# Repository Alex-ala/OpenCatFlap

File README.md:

OpenCatFlap
=====

Work in progress...

Being fed up with SurePets cat flap requiring cloud connection to properly work, I decided to design my own flap.
The 3D model is intended to fit into the SurePet adapter already installed.

I want my flap to have at least these features:
1. Easily managable via an API and/or WebUI/MQTT
2. Powered by battery OR power plug!
3. Easy install via AP/Wifi
4. Motion detection on both sides of the flap to check on where a cat is and where it moves to
5. Light barrier that detects into which direction the flap got opened
6. Light barrier in both sides of the "tunnel" to check into which direction the cat moved
7. Independent control of mechanic in and out control. (My cats outsmart SureFlap by letting each other out/in)
8. Two RFID sensors to detect cats on each side and possibly both!
9. Modular design to easily remove the cover, the electronics and the mechanical parts without having to unscrew screws from the outside.

In addition to that the software should be capable of everything SureFlap is capable of, plus:
1. Set pets as "outdoor only"
2. Quickly and more easily set specific per-cat permissions
3. Manually "unlock once" option for each direction

Current state:
------
**Hardware:**

It is bases on an ESP32 (Arduino Nano ESP32 for development) with various sensors and two servos to lock/unlock.
The 3D model is ready to be tested and a printed version is already in use to debug the code. Slight adjustments to the
antenna design will be done in future.

Used vital parts:
- 2x PIR (motion detection): Panasonic AMN33111, testing with cheaper options
- 2x light barrier for flap detection: TCST 1103
- 2x light barrier for tunnel passage: IR LED + NE555 and TSOP18*38 and TSOP18*56
- 2x RFID reader: EM4095
- 2x Servo: DSM44

**Software:**

The software runs a main process that handles global configs and aggregates events reported by the two state machines.
After the last hardware overhaul, quite some work is to be done to update sensors and reading RFID from EM4095 instead of WL-134

## State machines
The locking and unlocking logic is split up into two independent state machines, one for each direction of travel.
One state machine handles the PIR, RFID and Servo on one side of the cat flap.

This way the flap can idependently unlock for ougoing or incoing cats without acidentally opening the other direction aswell, allowing false passages.

Roughly speaking there are 3 states: Idle (only PIR active to wait for motion), Reading (RFID enabled when motion is detected) and unlocked (when a correct RFID is read).

## Wifi

If no Wifi is configured, the flap acts as an AP opening an open "OpenCatFlap" wifi. One can either use this wifi for full control via api, or send credentials to connect to an existing wifi.

## MQTT

MQTT can be configured to connect to an existing MQTT server. The flap will then send events to topics `opencatflap/<flapname>/<type>`.
Configuration via MQTT is planned.

## Webserver

Current means to configure the flap is via http. There is a webserver running on :80 that takes requests to configure wifi, mqtt, lock allowance and cats, aswell as getting some status information.

How to configure (for now):
Wifi: `curl -H "Content-Type: application/json" http://192.168.4.1/api -d '{"command": "wifiConfig", "ssid": "Bockenburg", "passphrase": "", "ntpServer": "ip preffered, hostname possible"}'`
MQTT: `curl -H "Content-Type: application/json" 'http://10.5.0.60/api' -d'{"command": "mqttConfig", "server": "mosquitto.ahome", "port": 8011, "ssl": true, "logActivity": true}'`
MQTT Certificates: 
```
curl -H "Content-Type: text/plain" 'http://10.5.0.60/api/certs?name=key' --data-binary @/home/alex/trash/opencatflap.key
curl -H "Content-Type: text/plain" 'http://10.5.0.60/api/certs?name=cert' --data-binary @/home/alex/trash/opencatflap.crt
curl -H "Content-Type: text/plain" 'http://10.5.0.60/api/certs?name=ca' --data-binary @/home/alex/trash/ca.crt
```

**Future Improvements:**
- NE555 is too inconsistant due to 5% tolerance capacitor with bad temperature coefficient
- Tuning condensators for EM4095 have to be bigger to allow more jiggle-room when building an antenna
- Condensators to configure EM4095 need to have better tolerance and temperature coefficient to get as close to required frequency as possible. Current ones allow reading big chips, small tubes and implanted ones need a lot of hugging the antenna.
- Cheaper connectors for the PCB and external sensors
- Battery backup circuit
- ESP32 directly onboard

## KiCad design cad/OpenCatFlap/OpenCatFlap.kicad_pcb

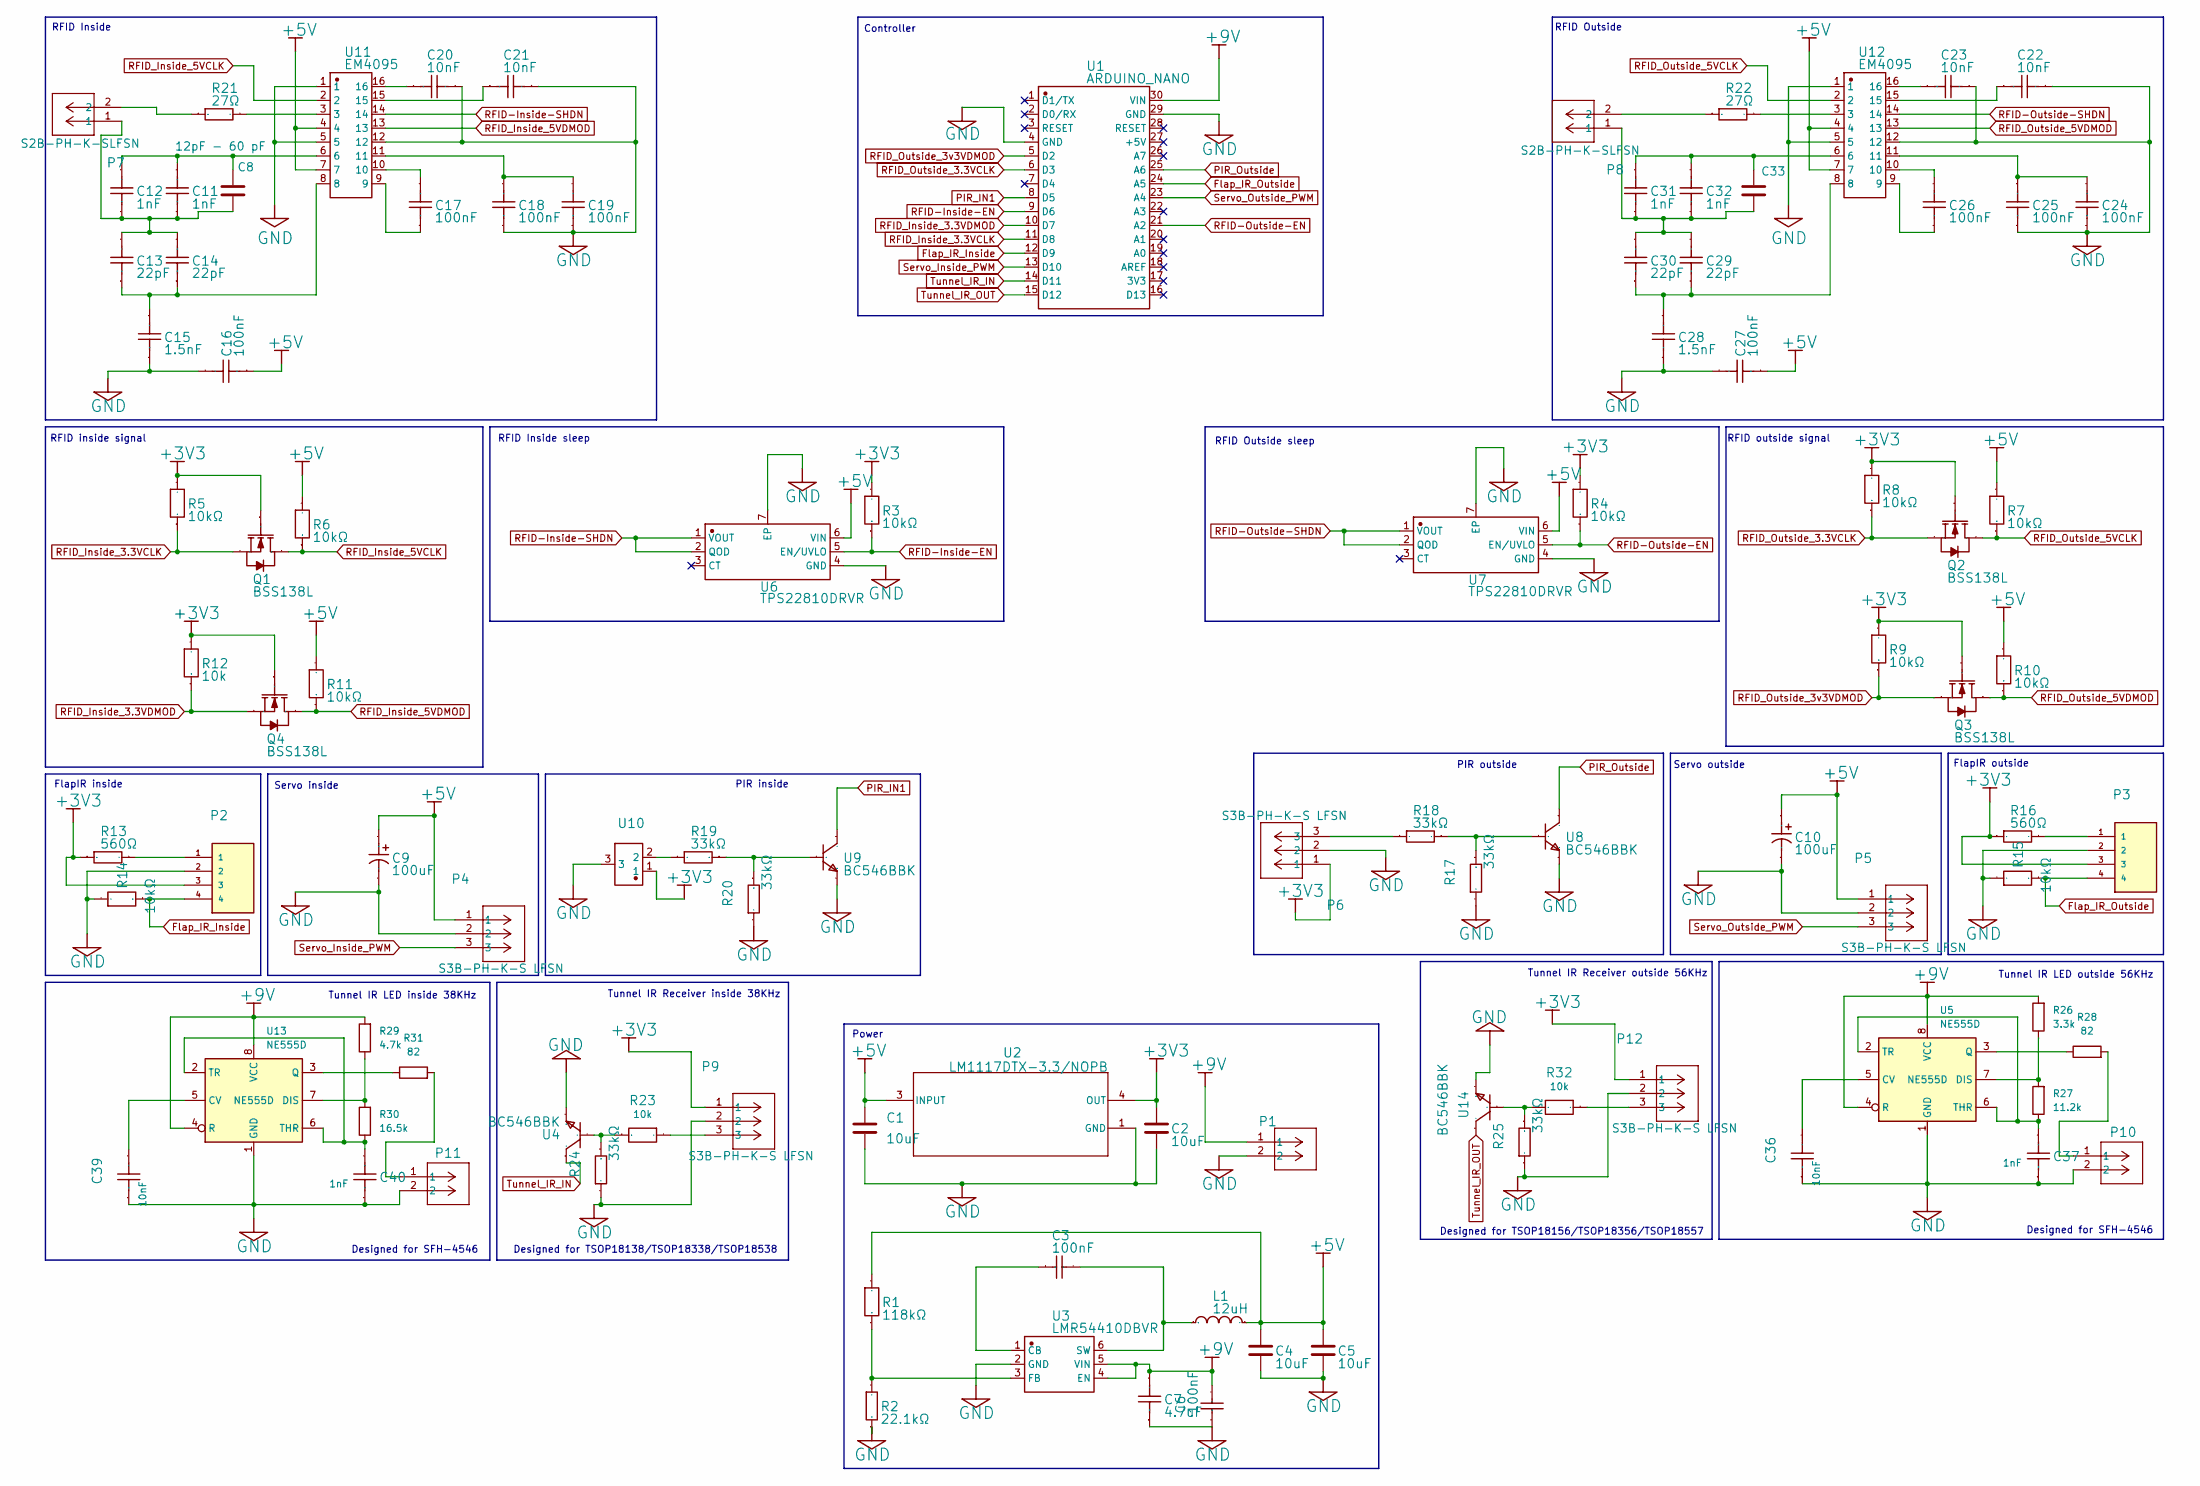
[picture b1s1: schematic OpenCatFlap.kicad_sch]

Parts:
C1, C2, C4, C5: 10uF; CAP_CL31A_SAM; Manufacturer Part CL31A106MBHNNNE
C3, C6: 100nF; C_1210_3225Metric; Manufacturer Part CC1210KKX7R0BB104
C7: 4.7uF; C_1206_3216Metric; Manufacturer Part CL31B475KPHNNNE
C8, C33: 12pF - 60 pF; VCAP_GKGXXX15_SGM; Manufacturer Part GKG30015
C9, C10: 100uF; CP_Elec_6.3x7.7; Manufacturer Part VH1E101ME077000CE0
C11, C12, C31, C32: 1nF; C_0603_1608Metric; Manufacturer Part CC0603JRX7R9BB102
C13, C14, C29, C30: 22pF; C_0603_1608Metric; Manufacturer Part 0603CG220J500NT
C15, C28: 1.5nF; C_0603_1608Metric; Manufacturer Part CL10B152KB8NNNC
C16, C17, C18, C19, C24, C25, C26, C27: 100nF; C_0603_1608Metric; Manufacturer Part CC0603KRX7R7BB104
C20, C21, C22, C23, C36, C39: 10nF; C_0603_1608Metric; Manufacturer Part CC0603KRX7R7BB103
C37, C40: 1nF; C_0603_1608Metric; Manufacturer Part 0603N102F160CT
L1: 12uH; LBM2016TI20J; Manufacturer Part LBM2016T120J
P1, P7, P8, P11: S2B-PH-K-SLFSN; CONN_S2B-PH-K-S_JST; Manufacturer Part S2B-PH-K-SLFSN
P2, P3: S4B-PH-K-S_LF__SN_; CONN_S4B-PH-K-S_JST; Manufacturer Part S4B-PH-K-S(LF)(SN)
P4, P5, P6, P9, P12: S3B-PH-K-S LFSN; CONN_S3B-PH-K-S_JST; Manufacturer Part S3B-PH-K-S LFSN
P10: IL-G-2P-S3T2-SA; CONN_S2B-PH-K-S_JST; Manufacturer Part S2B-PH-K-SLFSN
Q1, Q2, Q3, Q4: BSS138L; Manufacturer Part BSS138L
R1: 118kΩ; R_0603_1608Metric; Manufacturer Part RT0603FRE07118KL
R2: 22.1kΩ; R_0603_1608Metric; Manufacturer Part RC0603FR-0722K1L
R3, R4, R5, R6, R7, R8, R9, R10, R11, R14, R15: 10kΩ; R_0603_1608Metric; Manufacturer Part RC0603FR-0710KL
R12, R23, R32: 10k; R_0603_1608Metric; Manufacturer Part RC0603FR-0710KL
R13, R16: 560Ω; R_0603_1608Metric; Manufacturer Part AC0603FR-07560RL
R17, R18, R19, R20, R24, R25: 33kΩ; R_0603_1608Metric; Manufacturer Part RC0603FR-0733KL
R21, R22: 27Ω; R_0603_1608Metric; Manufacturer Part RC0603FR-0727RL
R26: 3.3k; R_0603_1608Metric; Manufacturer Part AC0603FR-073K3L
R27: 11.2k; R_0603_1608Metric; Manufacturer Part 0603WAF1122T5E
R28, R31: 82; R_0603_1608Metric; Manufacturer Part RC0603FR-0782RL
R29: 4.7k; R_0603_1608Metric; Manufacturer Part RC0603FR-074K7L
R30: 16.5k; R_0603_1608Metric; Manufacturer Part RC0603FR-0716K5L
U1: ARDUINO_NANO; Arduino Nano ESP32; Manufacturer Part 2x M20-7821546
U2: LM1117DTX-3.3/NOPB; LM1117DTX-3.3NOPB; Manufacturer Part LM1117DTX-3.3/NOPB
U3: LMR54410DBVR; U_SOT-23_TEX; Manufacturer Part LMR54410DBVR
U4, U8, U9, U14: BC546BBK; TO-92L_Inline; Manufacturer Part BC546BBK
U5, U13: NE555D; SOIC-8_3.9x4.9mm_P1.27mm; Manufacturer Part NE555D
U6, U7: TPS22810DRVR; DRV0006A_NV; Manufacturer Part TPS22810DRVR
U10: SENSOR MOTION SPOT 5V BLK LENS; AMN33111; Manufacturer Part AMN33111
U11, U12: EM4095; Manufacturer Part EM4095HMSO16B+

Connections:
+3V3: C2.1, P2.3, P3.3, P6.1, P9.1, P12.1, Q1.1 (G), Q2.1 (G), Q3.1 (G), Q4.1 (G), R3.2, R4.2, R5.2, R8.2, R9.2, R12.2, R13.1, R16.1, U2.4 (OUT), U10.1
+5V: C1.1, C4.1, C5.1, C9.1, C10.1, C16.1, C27.1, L1.2, P4.1, P5.1, R1.2, R6.2, R7.2, R10.2, R11.2, U2.3 (INPUT), U6.6 (VIN), U7.6 (VIN), U11.4, U11.7, U12.4, U12.7
+9V: C6.2, C7.2, P1.1, R26.2, R29.2, U1.30 (VIN), U3.4 (EN), U3.5 (VIN), U5.4 (R), U5.8 (VCC), U13.4 (R), U13.8 (VCC)
Flap_IR_Inside: P2.4, R14.1, U1.12 (D9)
Flap_IR_Outside: P3.4, R15.1, U1.24 (A5)
GND: C1.2, C2.2, C4.2, C5.2, C6.1, C7.1, C9.2, C10.2, C15.1, C16.2, C18.1, C19.1, C20.2, C21.2, C22.2, C23.2, C24.1, C25.1, C27.2, C28.1, C36.1, C37.1, C39.1, C40.1, P1.2, P2.2, P3.2, P4.2, P5.2, P6.2, P9.2, P10.2, P11.2, P12.2, R2.1, R14.2, R15.2, R17.2, R20.2, R24.2, R25.2, U1.4 (GND), U1.29 (GND), U2.1 (GND), U3.2 (GND), U4.3 (E), U5.1 (GND), U6.4 (GND), U6.7 (EP), U7.4 (GND), U7.7 (EP), U8.3 (E), U9.3 (E), U10.3, U11.1, U11.5, U11.12, U12.1, U12.5, U12.12, U13.1 (GND), U14.3 (E); also elsewhere on the board
unnamed: C8.1, C11.1, C12.1, C13.2, C14.2, P7.1
unnamed: C8.2, C11.2, C12.2, U11.6
unnamed: C13.1, C14.1, C15.2, U11.8
unnamed: C17.1, U11.9
unnamed: C17.2, U11.10
unnamed: C18.2, C19.2, U11.11
unnamed: C20.1, U11.16
unnamed: C21.1, U11.15
unnamed: C22.1, U12.15
unnamed: C23.1, U12.16
unnamed: C24.2, C25.2, U12.11
unnamed: C26.1, U12.9
unnamed: C26.2, U12.10
unnamed: C28.2, C29.1, C30.1, U12.8
unnamed: C29.2, C30.2, C31.1, C32.1, C33.1, P8.1
unnamed: C31.2, C32.2, C33.2, U12.6
unnamed: P2.1, R13.2
unnamed: P3.1, R16.2
unnamed: P6.3, R18.2
unnamed: P7.2, R21.1
unnamed: P8.2, R22.1
unnamed: P9.3, R23.2
unnamed: P10.1, R28.2
unnamed: P11.1, R31.2
unnamed: P12.3, R32.2
unnamed: R19.2, U10.2
unnamed: R21.2, U11.3
unnamed: R22.2, U12.3
unnamed: C3.1, U3.1 (CB)
unnamed: R1.1, R2.2, U3.3 (FB)
unnamed: C3.2, L1.1, U3.6 (SW)
unnamed: R23.1, R24.1, U4.2 (B)
unnamed: C36.2, U5.5 (CV)
unnamed: R26.1, R27.2, U5.7 (DIS)
unnamed: R28.1, U5.3 (Q)
unnamed: C37.2, R27.1, U5.2 (TR), U5.6 (THR)
unnamed: R17.1, R18.1, U8.2 (B)
unnamed: R19.1, R20.1, U9.2 (B)
unnamed: C39.2, U13.5 (CV)
unnamed: R29.1, R30.2, U13.7 (DIS)
unnamed: R31.1, U13.3 (Q)
unnamed: C40.2, R30.1, U13.2 (TR), U13.6 (THR)
unnamed: R25.1, R32.1, U14.2 (B)
PIR_IN1: U1.8 (D5), U9.1 (C)
PIR_Outside: U1.25 (A6), U8.1 (C)
RFID-Inside-EN: R3.1, U1.9 (D6), U6.5 (EN/UVLO)
RFID-Inside-SHDN: U6.1 (VOUT), U6.2 (QOD), U11.14
RFID-Outside-EN: R4.1, U1.21 (A2), U7.5 (EN/UVLO)
RFID-Outside-SHDN: U7.1 (VOUT), U7.2 (QOD), U12.14
RFID_Inside_3.3VCLK: Q1.2 (S), R5.1, U1.11 (D8)
RFID_Inside_3.3VDMOD: Q4.2 (S), R12.1, U1.10 (D7)
RFID_Inside_5VCLK: Q1.3 (D), R6.1, U11.2
RFID_Inside_5VDMOD: Q4.3 (D), R11.1, U11.13
RFID_Outside_3.3VCLK: Q2.2 (S), R8.1, U1.6 (D3)
RFID_Outside_3v3VDMOD: Q3.2 (S), R9.1, U1.5 (D2)
RFID_Outside_5VCLK: Q2.3 (D), R7.1, U12.2
RFID_Outside_5VDMOD: Q3.3 (D), R10.1, U12.13
Servo_Inside_PWM: P4.3, U1.13 (D10)
Servo_Outside_PWM: P5.3, U1.23 (A4)
Tunnel_IR_IN: U1.14 (D11), U4.1 (C)
Tunnel_IR_OUT: U1.15 (D12), U14.1 (C)

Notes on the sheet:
FlapIR inside
Tunnel IR Receiver outside 56KHz
FlapIR outside
Designed for TSOP18138/TSOP18338/TSOP18538
Controller
PIR outside
Tunnel IR LED inside 38KHz
Servo outside
Designed for SFH-4546
Designed for TSOP18156/TSOP18356/TSOP18557
RFID Outside
RFID inside signal
RFID Outside sleep
Power
Servo inside
RFID outside signal
PIR inside
RFID Inside
RFID Inside sleep
Tunnel IR LED outside 56KHz
Tunnel IR Receiver inside 38KHz

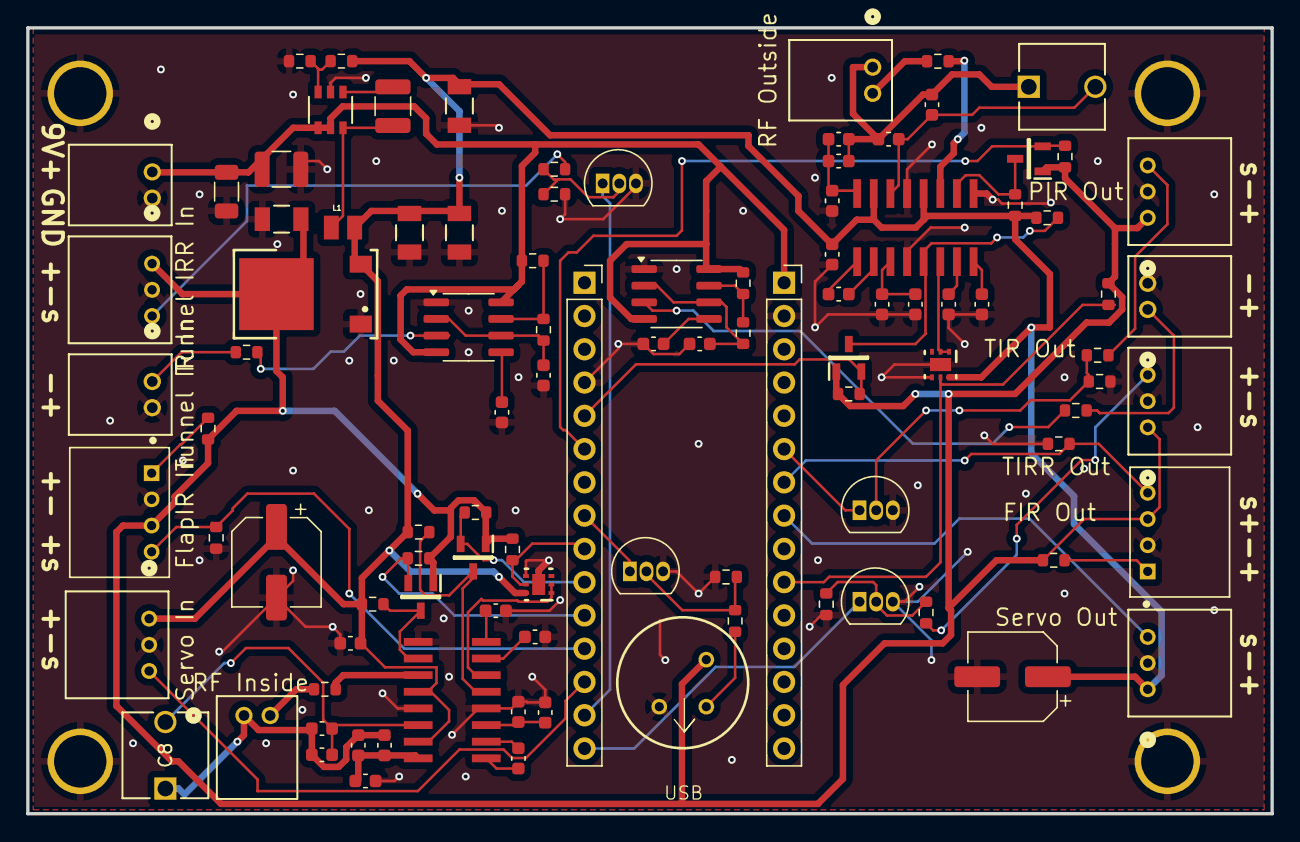
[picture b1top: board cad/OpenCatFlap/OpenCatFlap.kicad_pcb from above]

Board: 2 copper layers, 95.0 x 60.0 mm, 104 parts (1 on the bottom side), 67 nets.

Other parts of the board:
Pad_gge19202, Pad_gge19226, Pad_gge19274, Pad_gge19274#2: Bohrloch

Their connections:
GND: Pad_gge19202.1, Pad_gge19226.1, Pad_gge19274.1, Pad_gge19274#2.1; also elsewhere on the board

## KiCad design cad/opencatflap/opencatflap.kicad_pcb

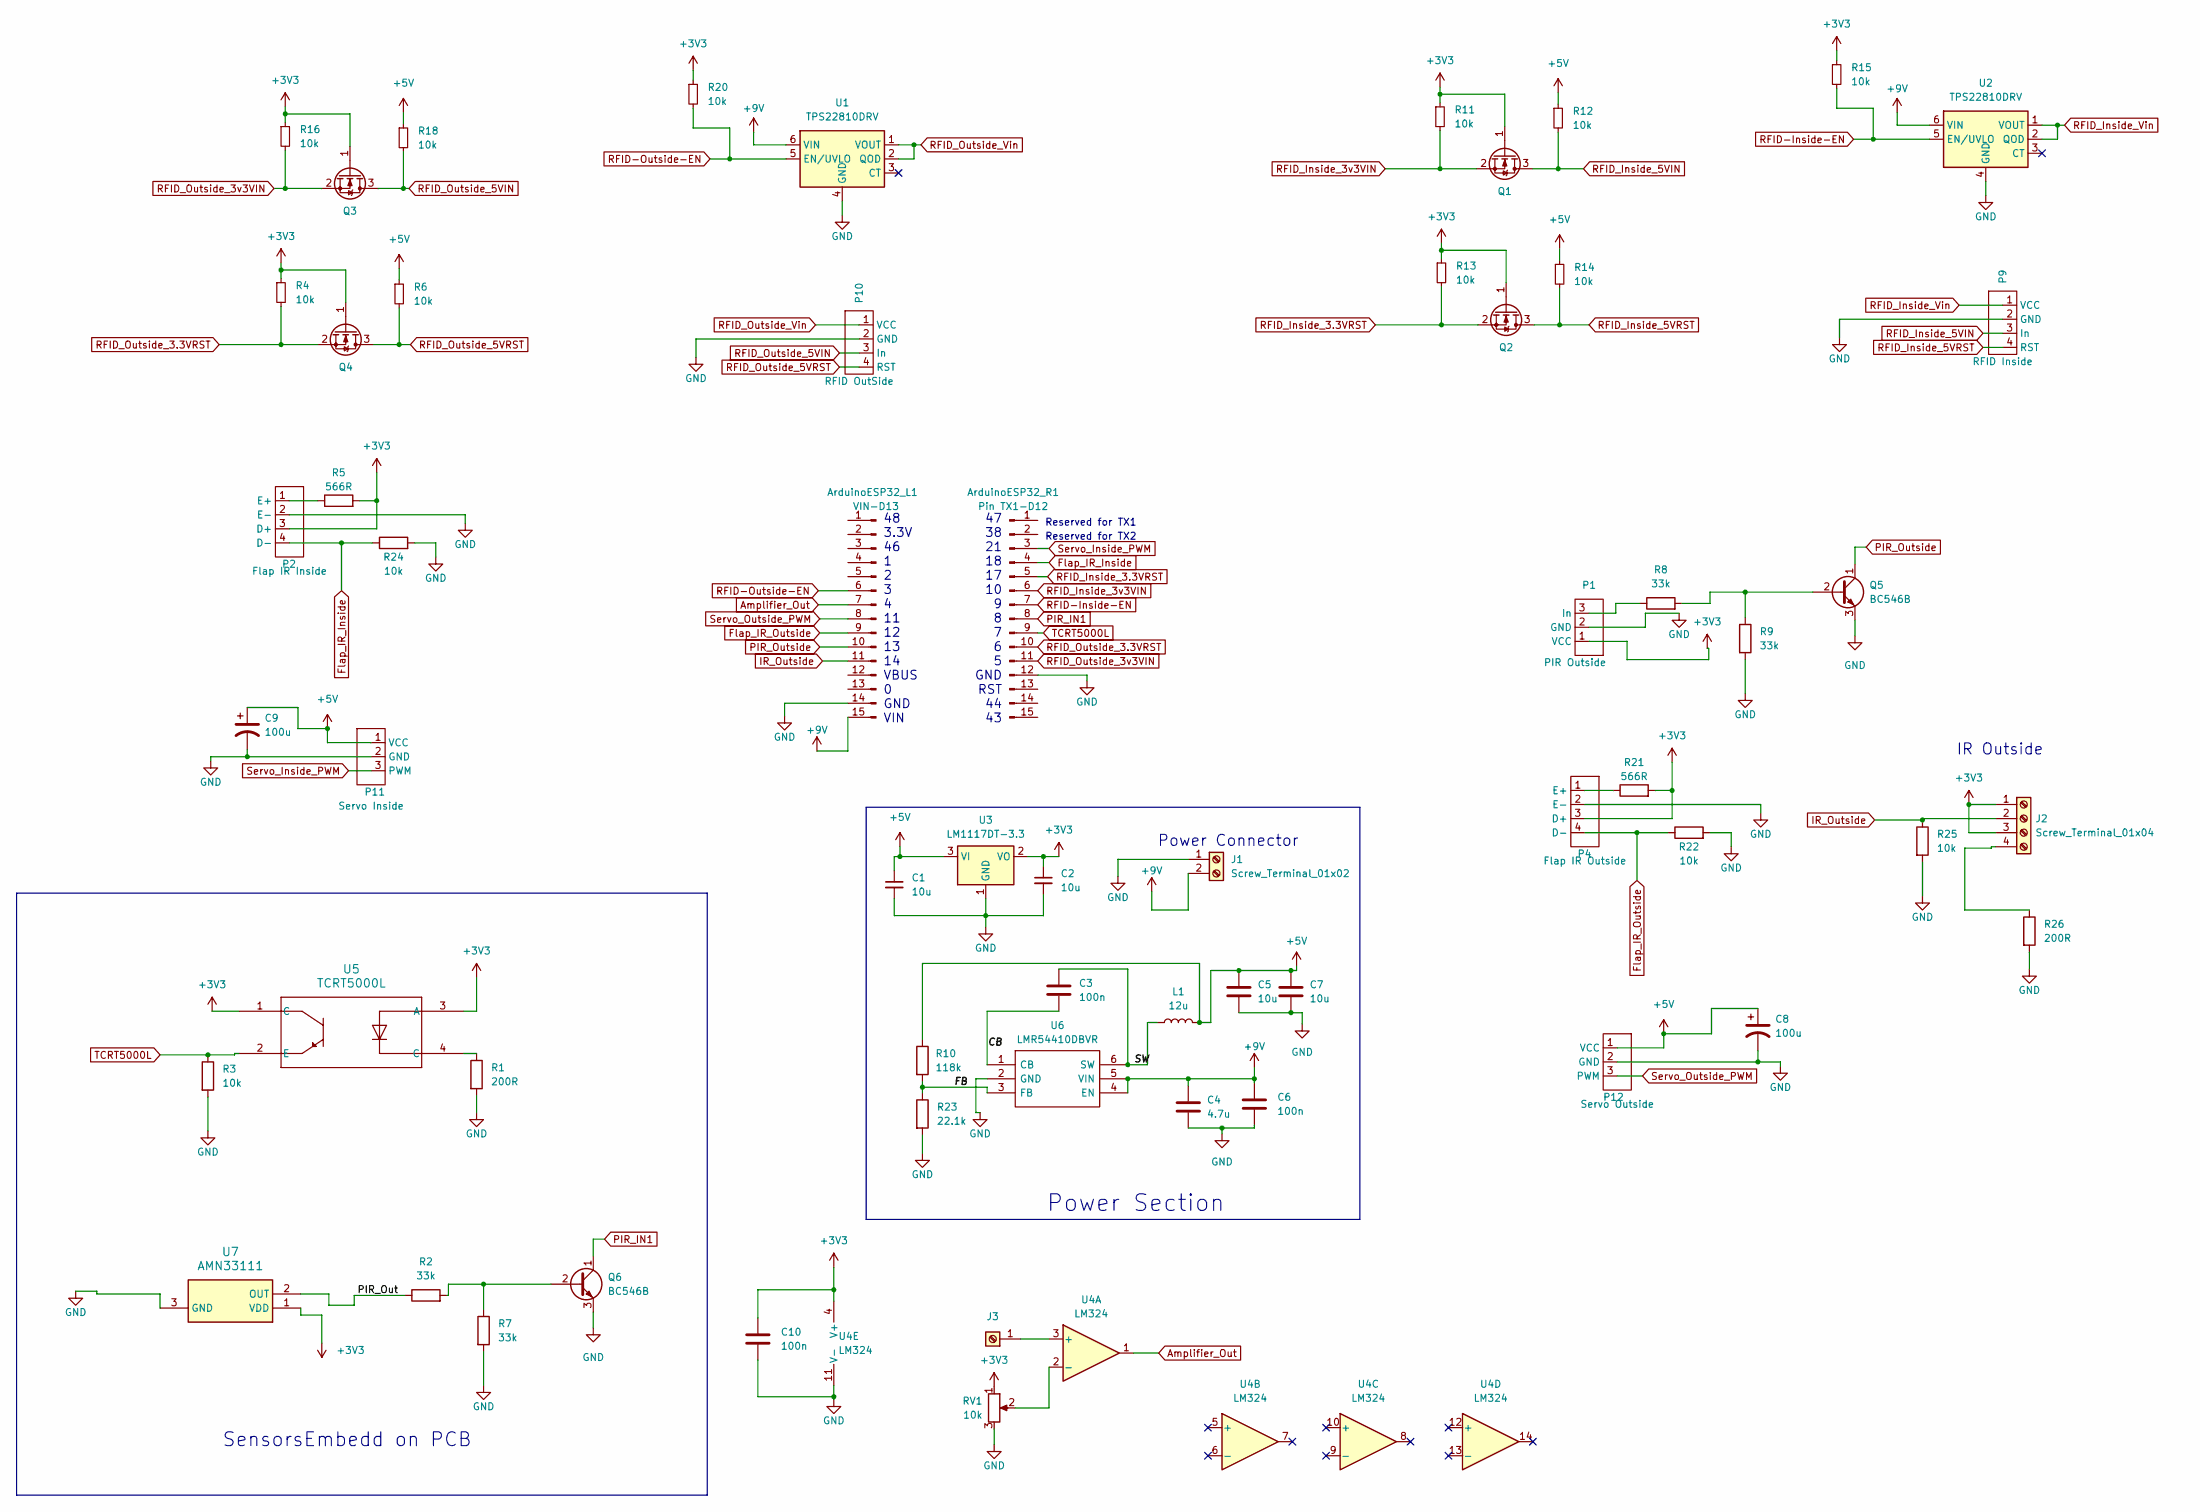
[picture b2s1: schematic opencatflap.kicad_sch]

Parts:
ArduinoESP32_L1: VIN-D13; PinHeader_1x15_P2.54mm_Vertical
ArduinoESP32_R1: Pin TX1-D12; PinHeader_1x15_P2.54mm_Vertical
C1, C2: 10u; C_0805_2012Metric
C3: 100n; C_0402_1005Metric; LCSC C71629
C4: 4.7u; C_1210_3225Metric; LCSC C86052
C5, C7: 10u; C_0805_2012Metric; LCSC C15850
C6, C10: 100n; C_0603_1608Metric; LCSC C14663
C8, C9: 100u; CP_Elec_6.3x7.7; Manufacturer Part # RVT1V101M0607
J1: Screw_Terminal_01x02; TerminalBlock_4Ucon_1x02_P3.50mm_Vertical; Manufacturer Part # DB301V-3.5-2P-GN-S
J2: Screw_Terminal_01x04; PinHeader_1x04_P2.54mm_Vertical
J3: Screw_Terminal_01x01; PinHeader_1x01_P2.54mm_Vertical; Manufacturer Part # 2.54-1*1P
L1: 12u; SDR0805120ML; LCSC C168035
P1: PIR Outside; PinHeader_1x03_P2.54mm_Vertical
P2: Flap IR Inside; PinHeader_1x04_P2.54mm_Vertical
P4: Flap IR Outside; PinHeader_1x04_P2.54mm_Vertical
P9: RFID Inside; PinHeader_1x04_P2.54mm_Vertical
P10: RFID OutSide; PinHeader_1x04_P2.54mm_Vertical
P11: Servo Inside; PinHeader_1x03_P2.54mm_Vertical
P12: Servo Outside; PinHeader_1x03_P2.54mm_Vertical
Q1, Q2, Q3, Q4: BSS138; SOT-23; Manufactuer Part # BSS138
Q5, Q6: BC546B; TO-92_Inline; Manufacturer Part # BC546B
R1, R26: 200R; R_0603_1608Metric
R2, R7, R8, R9: 33k; R_0603_1608Metric
R3, R4, R6, R11, R12, R13, R14, R15, R16, R18, R20, R22, R24, R25: 10k; R_0603_1608Metric
R5, R21: 566R; R_0603_1608Metric
R10: 118k; R_0402_1005Metric; LCSC C5126219
R23: 22.1k; R_0402_1005Metric; LCSC C844504
RV1: 10k; 3296W-1; Manufacturer Part # 3296W-1-103LF
U1, U2: TPS22810DRV; WSON-6-1EP_2x2mm_P0.65mm_EP1x1.6mm; Manufacturer Part # TPS22810DRVR
U3: LM1117DT-3.3; TO-252-3_TabPin2; Manufacturer Part # LM1117DT-3.3/NOPB
U4: LM324; SOIC127P600X175-14N; Manufacturer Part # LM324
U5: TCRT5000L; Manufacturer Part # TCRT5000L
U6: LMR54410DBVR; Manufacturer_Part_Number LMR54410DBVR; Mouser Part Number 595-LMR54410DBVR
U7: AMN33111; Manufcture Part # AMN33111

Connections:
+3V3: C2.1, C10.1, J2.1, J2.3, P1.1 (VCC), P2.3 (D+), P4.3 (D+), Q1.1 (G), Q2.1 (G), Q3.1 (G), Q4.1 (G), R4.1, R5.2, R11.1, R13.1, R15.1, R16.1, R20.1, R21.2, RV1.1, U3.2 (VO), U4.4 (V+), U5.1 (C), U5.3 (A), U7.1 (VDD)
+5V: C1.1, C5.1, C7.1, C8.1, C9.1, L1.2, P11.1 (VCC), P12.1 (VCC), R6.1, R10.1, R12.1, R14.1, R18.1, U3.3 (VI)
+9V: ArduinoESP32_L1.15, C4.1, C6.1, J1.2, U1.6 (VIN), U2.6 (VIN), U6.4 (EN), U6.5 (VIN)
/CB: C3.2, U6.1 (CB)
/FB: R10.2, R23.1, U6.3 (FB)
/PIR_Out: R2.1, U7.2 (OUT)
/SW: C3.1, L1.1, U6.6 (SW)
Amplifier_Out: ArduinoESP32_L1.7, U4.1
Flap_IR_Inside: ArduinoESP32_R1.4, P2.4 (D-), R24.1
Flap_IR_Outside: ArduinoESP32_L1.9, P4.4 (D-), R22.1
GND: ArduinoESP32_L1.14, ArduinoESP32_R1.12, C1.2, C2.2, C4.2, C5.2, C6.2, C7.2, C8.2, C9.2, C10.2, J1.1, P1.2 (GND), P2.2 (E-), P4.2 (E-), P9.2 (GND), P10.2 (GND), P11.2 (GND), P12.2 (GND), Q5.3 (E), Q6.3 (E), R1.2, R3.2, R7.2, R9.2, R22.2, R23.2, R24.2, R25.2, R26.2, RV1.3, U1.4 (GND), U1.7 (GND), U2.4 (GND), U2.7 (GND), U3.1 (GND), U4.11 (V-), U6.2 (GND), U7.3 (GND)
IR_Outside: ArduinoESP32_L1.11, J2.2, R25.1
unnamed: J2.4, R26.1
unnamed: J3.1, U4.3 (+)
unnamed: P1.3 (In), R8.1
unnamed: P2.1 (E+), R5.1
unnamed: P4.1 (E+), R21.1
unnamed: Q5.2 (B), R8.2, R9.1
unnamed: Q6.2 (B), R2.2, R7.1
unnamed: R1.1, U5.4 (C)
unnamed: RV1.2, U4.2 (-)
PIR_IN1: ArduinoESP32_R1.8, Q6.1 (C)
PIR_Outside: ArduinoESP32_L1.10, Q5.1 (C)
RFID-Inside-EN: ArduinoESP32_R1.7, R15.2, U2.5 (EN/UVLO)
RFID-Outside-EN: ArduinoESP32_L1.6, R20.2, U1.5 (EN/UVLO)
RFID_Inside_3.3VRST: ArduinoESP32_R1.5, Q2.2 (S), R13.2
RFID_Inside_3v3VIN: ArduinoESP32_R1.6, Q1.2 (S), R11.2
RFID_Inside_5VIN: P9.3 (In), Q1.3 (D), R12.2
RFID_Inside_5VRST: P9.4 (RST), Q2.3 (D), R14.2
RFID_Inside_Vin: P9.1 (VCC), U2.1 (VOUT), U2.2 (QOD)
RFID_Outside_3.3VRST: ArduinoESP32_R1.10, Q4.2 (S), R4.2
RFID_Outside_3v3VIN: ArduinoESP32_R1.11, Q3.2 (S), R16.2
RFID_Outside_5VIN: P10.3 (In), Q3.3 (D), R18.2
RFID_Outside_5VRST: P10.4 (RST), Q4.3 (D), R6.2
RFID_Outside_Vin: P10.1 (VCC), U1.1 (VOUT), U1.2 (QOD)
Servo_Inside_PWM: ArduinoESP32_R1.3, P11.3 (PWM)
Servo_Outside_PWM: ArduinoESP32_L1.8, P12.3 (PWM)
TCRT5000L: ArduinoESP32_R1.9, R3.1, U5.2 (E)

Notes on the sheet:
Reserved for TX2
48 3.3V 46 1 2 3 4 11 12 13 14 VBUS 0 GND VIN
47 38 21 18 17 10 9 8 7 6 5 GND RST 44 43
Power Connector
SensorsEmbedd on PCB
Reserved for TX1
IR Outside
Power Section

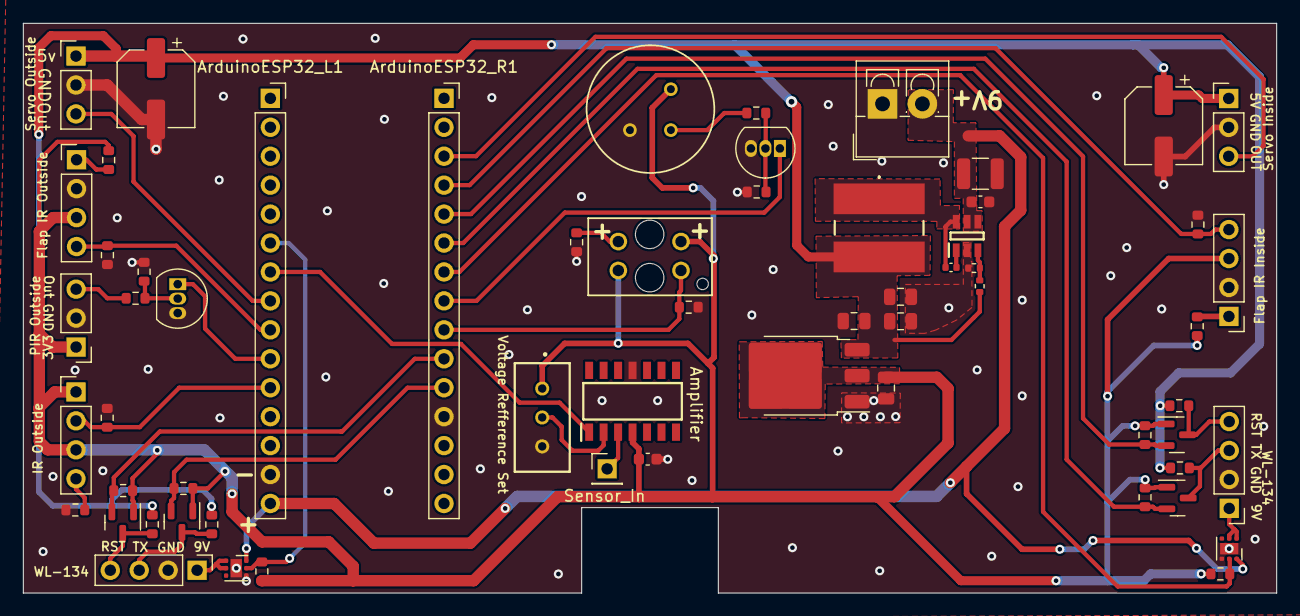
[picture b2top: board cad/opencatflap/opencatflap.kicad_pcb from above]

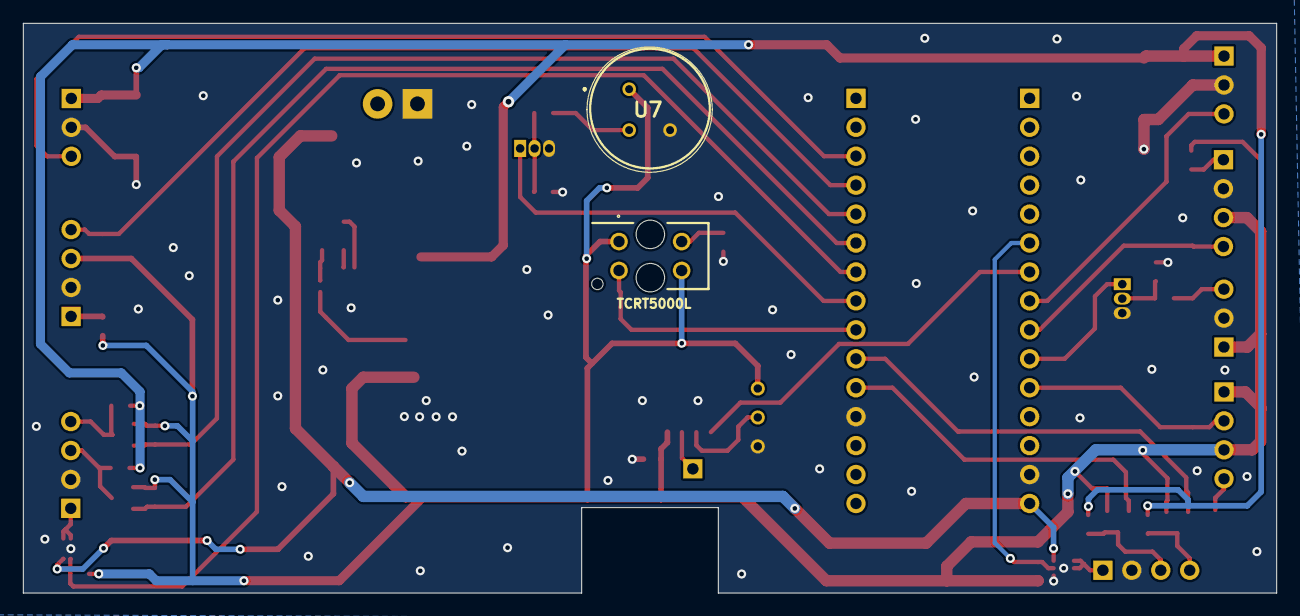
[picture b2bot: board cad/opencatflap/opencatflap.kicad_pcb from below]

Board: 2 copper layers, 110.0 x 50.0 mm, 61 parts (2 on the bottom side), 38 nets.

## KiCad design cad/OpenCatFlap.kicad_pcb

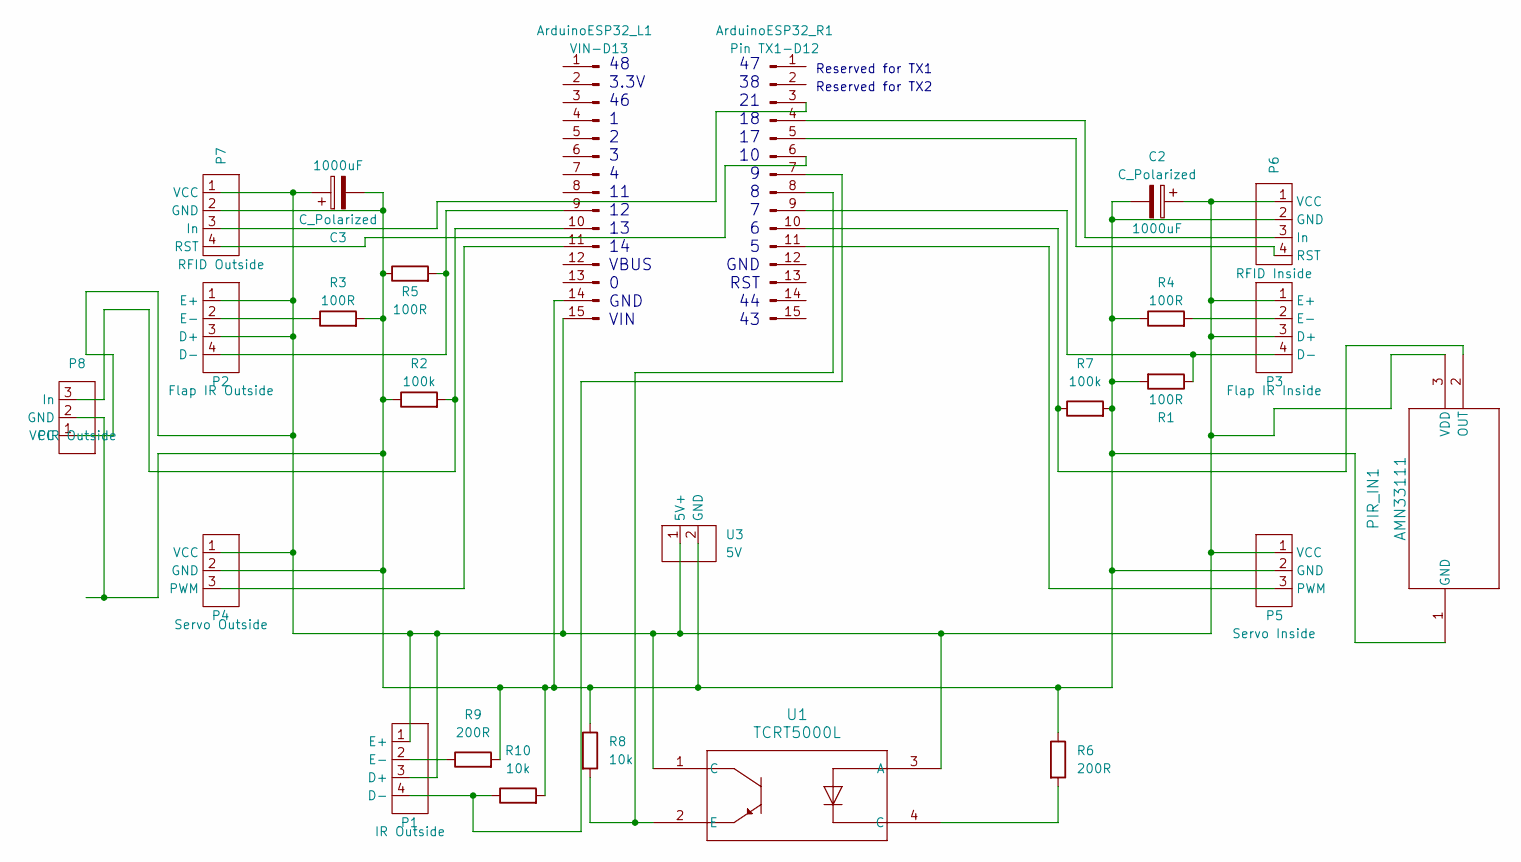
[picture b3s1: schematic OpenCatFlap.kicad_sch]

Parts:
ArduinoESP32_L1: VIN-D13; PinHeader_1x15_P2.54mm_Vertical
ArduinoESP32_R1: Pin TX1-D12; PinHeader_1x15_P2.54mm_Vertical
C2, C3: C_Polarized; CP_Elec_8x10
P1: IR Outside; PinHeader_1x04_P2.54mm_Vertical
P2: Flap IR Outside; PinHeader_1x04_P2.54mm_Vertical
P3: Flap IR Inside; PinHeader_1x04_P2.54mm_Vertical
P4: Servo Outside; PinHeader_1x03_P2.54mm_Vertical
P5: Servo Inside; PinHeader_1x03_P2.54mm_Vertical
P6: RFID Inside; PinHeader_1x04_P2.54mm_Vertical
P7: RFID Outside; PinHeader_1x04_P2.54mm_Vertical
P8: PIR Outside; PinHeader_1x03_P2.54mm_Vertical
PIR_IN1: AMN33111; AMN33111_PAN
R1, R3, R4, R5: 100R; R_0805_2012Metric
R2, R7: 100k; R_0805_2012Metric
R6, R9: 200R; R_0805_2012Metric
R8, R10: 10k; R_0805_2012Metric
U1: TCRT5000L; TCRT5000_VIS
U3: 5V; PinHeader_1x02_P2.54mm_Vertical

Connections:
unnamed: ArduinoESP32_L1.9, P2.4 (D-), R5.2
unnamed: ArduinoESP32_L1.10, P8.3 (In), R2.2
unnamed: ArduinoESP32_L1.11, P4.3 (PWM)
unnamed: ArduinoESP32_L1.14, C2.2, C3.2, P4.2 (GND), P5.2 (GND), P6.2 (GND), P7.2 (GND), P8.2 (GND), PIR_IN1.1 (GND), R1.2, R2.1, R3.2, R4.1, R5.1, R6.1, R7.2, R8.1, R9.2, R10.2, U3.2 (GND)
unnamed: ArduinoESP32_L1.15, C2.1, C3.1, P1.1 (E+), P1.3 (D+), P2.1 (E+), P2.3 (D+), P3.1 (E+), P3.3 (D+), P4.1 (VCC), P5.1 (VCC), P6.1 (VCC), P7.1 (VCC), P8.1 (VCC), PIR_IN1.3 (VDD), U1.1 (C), U1.3 (A), U3.1 (5V+)
unnamed: ArduinoESP32_R1.3, P7.3 (In)
unnamed: ArduinoESP32_R1.4, P6.3 (In)
unnamed: ArduinoESP32_R1.5, P6.4 (RST)
unnamed: ArduinoESP32_R1.6, P7.4 (RST)
unnamed: ArduinoESP32_R1.7, P1.4 (D-), R10.1
unnamed: ArduinoESP32_R1.8, R8.2, U1.2 (E)
unnamed: ArduinoESP32_R1.9, P3.4 (D-), R1.1
unnamed: ArduinoESP32_R1.10, PIR_IN1.2 (OUT), R7.1
unnamed: ArduinoESP32_R1.11, P5.3 (PWM)
unnamed: P1.2 (E-), R9.1
unnamed: P2.2 (E-), R3.1
unnamed: P3.2 (E-), R4.2
unnamed: R6.2, U1.4 (C)

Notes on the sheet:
Reserved for TX2
48 3.3V 46 1 2 3 4 11 12 13 14 VBUS 0 GND VIN
47 38 21 18 17 10 9 8 7 6 5 GND RST 44 43
Reserved for TX1

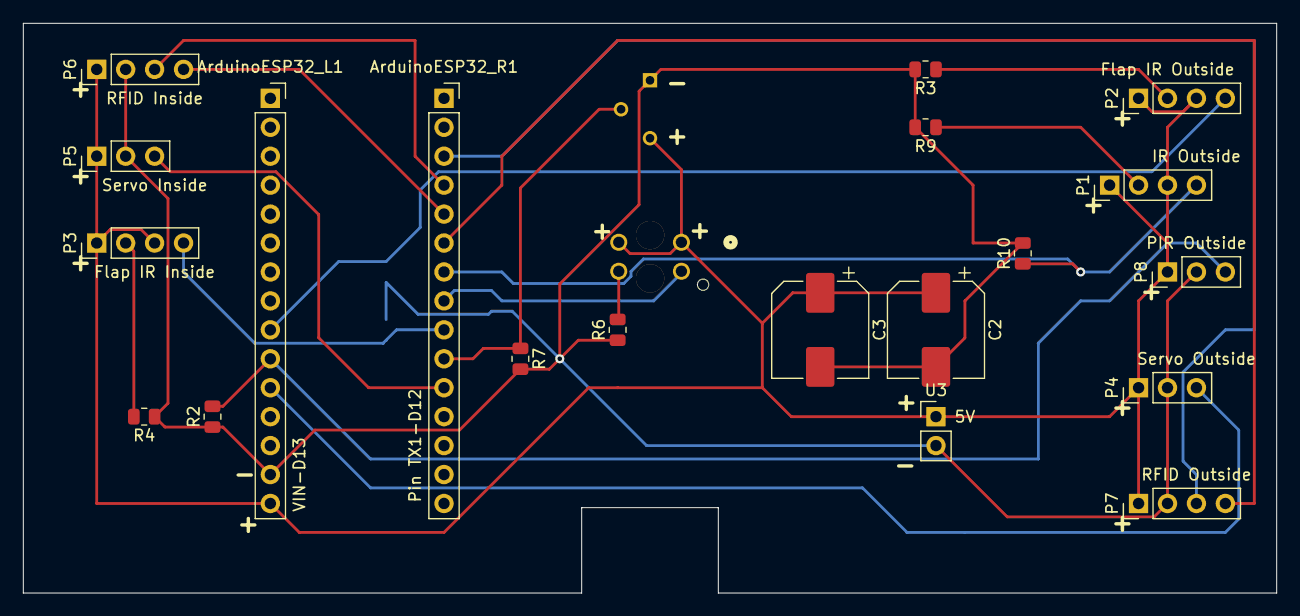
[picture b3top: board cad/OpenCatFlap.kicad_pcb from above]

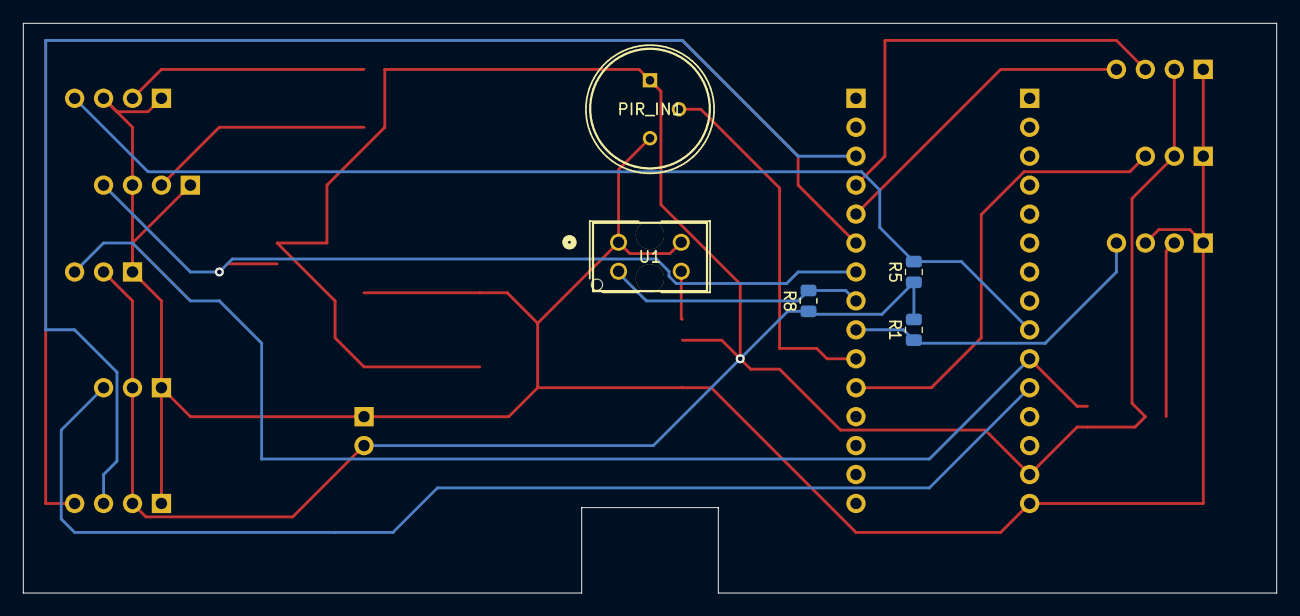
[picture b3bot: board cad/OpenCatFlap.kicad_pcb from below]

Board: 2 copper layers, 110.0 x 50.0 mm, 25 parts (5 on the bottom side), 18 nets.

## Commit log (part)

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2023-06-03 Init
2023-06-03 removed asynchttpserver dependency
2023-06-03 add more definitions to start with hardware implementation
2023-06-03 Test lock control via debug endpoint. Automatically lock after 2s
2023-06-04 debug motion sensors
2023-06-10 line feeds. And motion control
2023-06-10 persist state
2023-06-11 hurz
2023-06-16 Prepare for evaluation run
2023-06-16 more robust opening/closing
2023-06-17 Test direction detection
2023-06-17 Better value for inside servo
2023-06-17 Use NTP
2023-07-08 woop woop works without intereferences now
2023-07-08 add bad schematics
2023-07-15 meowqtt
2023-09-10 add cad
2023-09-10 meowqtt works
2023-09-10 more mqtt
2023-09-18 make everything ugly, but OOP LUL
2023-09-19 improvements
2023-10-13 meow
2023-10-14 update readme with parts
2023-10-15 Revert "meow"
    This reverts commit 70150f40207d0a9de3da7c8185f4e8c8306b4b66.
2023-10-21 repo cleanup
2023-10-30 add rfid init
2024-01-02 boop
2024-01-03 Fix wiring
2024-03-28 board v2
2024-03-28 update schematics
2024-07-06 Run on new mainboard
2024-07-07 rfid test
2024-07-07 test rfid, update cad
2024-08-11 initial work
2024-08-11 blurgh
2024-09-22 statemachine
2024-10-05 Fix compile
2024-10-13 it compiles. No clue if it runs
2024-10-14 roughly working version
2024-12-01 fix rfid
2024-12-14 wörk
2024-12-14 cat control working
2024-12-14 remove old files
2024-12-15 mqtt, fix rfid logging, add html config
2024-12-21 add mqtt messages for rfid and locks
2025-07-20 init new rfid tests
2025-07-20 rfid works-ish (need checksum tests)
2025-10-05 cleanup
2025-12-13 works
2025-12-13 a little beautify
2025-12-13 rearrange
2025-12-16 Not functional yet, but first todos to go with new RFID code.
2025-12-21 test
2025-12-22 RFID works. no logic implemented yet
2026-01-18 init logic
